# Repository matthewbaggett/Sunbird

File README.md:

# Sunbird

Version: rev11.

## Technical information

This is a board designed around an off-the-shelf ESP8266 ESP-12(E|F|S) module.

### Component choices

 * [ESP8266](./docs/esp8266ex.pdf) single-core 160Mhz 32 bit microcontroller with Wifi, 32K RAM and 4MB ROM as main CPU.
 * 2x 5050 RGB notification LEDs on either side of the PCB at the rear end
 * USB C charge and programming port.
 * [CH340g](./docs/CH340DS1.pdf) USB UART controller, with automatic reset circuitry for programming CPU.
 * [FS312F-G](./docs/FS312F-G-DS-10_EN.pdf) (and associated double-mosfet) short circuit protection circuitry. This also provides overcharge/overdischarge protection
 * [TP4056](./docs/TP4056.pdf) li-ion battery charger circuit. CHRG and STDBY signals passed through to CPU.
 * [ADXL345](./docs/ADXL345.pdf) Accellerometer for smart-power-off and usage detection using i2c bus with interrupt line.
 * [FM116B](./docs/FM116B.pdf) motor driver H-bridge IC. Warning: Datasheet almost entirely in Chinese.
 * Integrated 500mA fuse on PCB.
 * Standardised around 0603 size components where possible.
 * [Tag-Connect TC2030 no-legs](http://www.tag-connect.com/TC2030-MCP-NL) zero-pcb-parts connector used for programming and debugging before the CH340G is brought up, and for diagnosis when the CH340G is not populated, or otherwise unavailable due to failure.

### Technical features

 * Ability to field-program in-situ using USB bus.
 * Ability to OTA (Over The Air) program device.
 * Ability to sample battery voltage without incurring passive current draw, using 2 high-resistence resistors and a single transitor to enable battery sampling.
 * Ability to run while charging battery.
 * Ability to show status using RGB colour LED on both sides of circuit board.

### Known issues
 * 3.3v regulator has been problematic so far. Hopefully resolved in rev11.
 * 5050 RGB LEDs don't have consistent pinout of which colour channel is on which pin, meaning the value of R8020-22 are unpredictable, and subject to change before assembly. I have debated using WS2812B or similar as a replacement, but increasing parts cost and program complexity deterred me.

### Licencing

Sunbird is licenced under the [Open Hardware TAPR licence](./LICENCE.md).

## PCB

## Schematics

### Processor

### Battery Charger Circuit

### Power Regulator

### Motor Driver

### USB UART

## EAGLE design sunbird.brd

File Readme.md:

# Sunbird

Version: rev11.

## Technical information

This is a board designed around an off-the-shelf ESP8266 ESP-12(E|F|S) module.

### Component choices

 * [ESP8266](./docs/esp8266ex.pdf) single-core 160Mhz 32 bit microcontroller with Wifi, 32K RAM and 4MB ROM as main CPU.
 * 2x 5050 RGB notification LEDs on either side of the PCB at the rear end
 * USB C charge and programming port.
 * [CH340g](./docs/CH340DS1.pdf) USB UART controller, with automatic reset circuitry for programming CPU.
 * [FS312F-G](./docs/FS312F-G-DS-10_EN.pdf) (and associated double-mosfet) short circuit protection circuitry. This also provides overcharge/overdischarge protection
 * [TP4056](./docs/TP4056.pdf) li-ion battery charger circuit. CHRG and STDBY signals passed through to CPU.
 * [ADXL345](./docs/ADXL345.pdf) Accellerometer for smart-power-off and usage detection using i2c bus with interrupt line.
 * [FM116B](./docs/FM116B.pdf) motor driver H-bridge IC. Warning: Datasheet almost entirely in Chinese.
 * Integrated 500mA fuse on PCB.
 * Standardised around 0603 size components where possible.
 * [Tag-Connect TC2030 no-legs](http://www.tag-connect.com/TC2030-MCP-NL) zero-pcb-parts connector used for programming and debugging before the CH340G is brought up, and for diagnosis when the CH340G is not populated, or otherwise unavailable due to failure.

### Technical features

 * Ability to field-program in-situ using USB bus.
 * Ability to OTA (Over The Air) program device.
 * Ability to sample battery voltage without incurring passive current draw, using 2 high-resistence resistors and a single transitor to enable battery sampling.
 * Ability to run while charging battery.
 * Ability to show status using RGB colour LED on both sides of circuit board.

### Known issues
 * 3.3v regulator has been problematic so far. Hopefully resolved in rev11.
 * 5050 RGB LEDs don't have consistent pinout of which colour channel is on which pin, meaning the value of R8020-22 are unpredictable, and subject to change before assembly. I have debated using WS2812B or similar as a replacement, but increasing parts cost and program complexity deterred me.

## PCB
![Render][./images/3d.png]
![PCB view][./images/pcb.png]

## Schematics

### Processor
![Processor][./images/processor.png]

### Battery Charger Circuit
![Battery Charger][./images/battery_charger.png]

### Power Regulator
![Power Regulator][./images/power_regulator.png]

### Motor Driver
![Motor Driver][./images/motor_driver.png]

### USB UART
![USB UART][./images/usb_uart_ch340g.png]

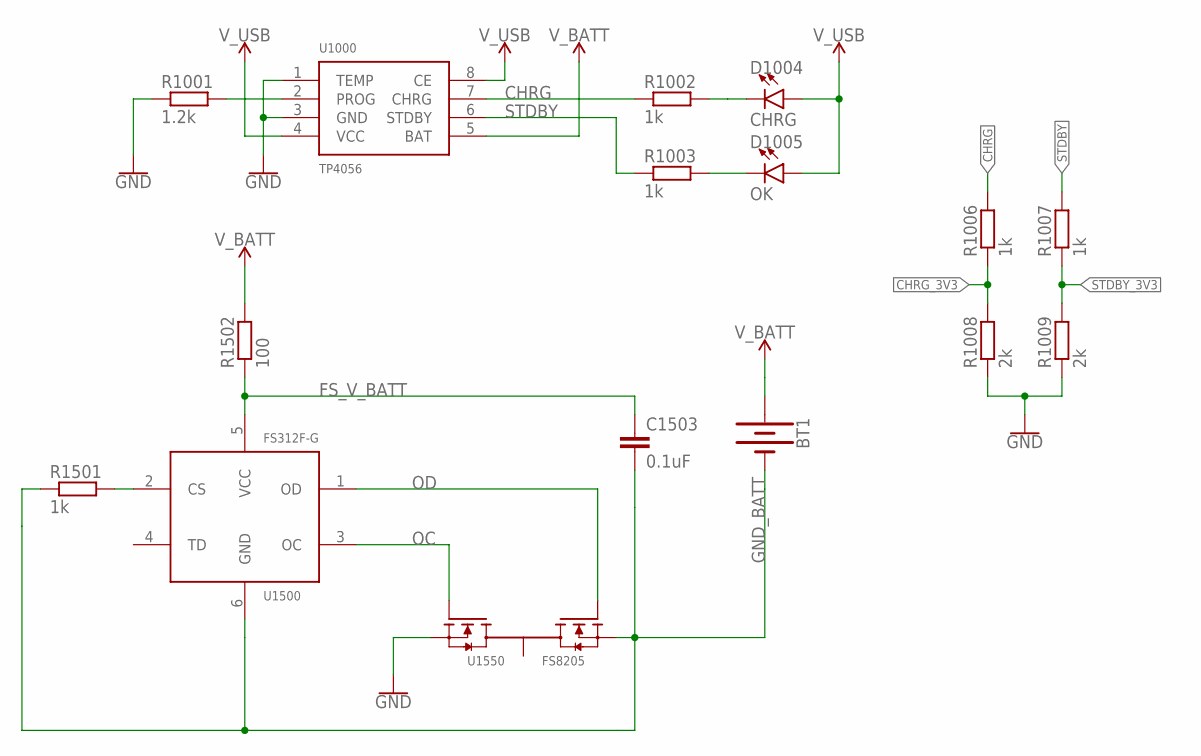
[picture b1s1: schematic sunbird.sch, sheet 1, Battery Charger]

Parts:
BT1: BATTERY-18650; BATTERY_18650-HOLDER
C1503: 0.1uF; C0603
D1004: CHRG; LED-0603
D1005: OK; LED-0603
R1001: 1.2k; R0603
R1002, R1003, R1006, R1007, R1501: 1k; R0603
R1008, R1009: 2k; R0603
R1502: 100; R0603
U1000: TP4056; SOP-8-THERMAL
U1500: FS312F-G; SOT23-6
U1550: FS8205; SOT23-6

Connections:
CHRG: R1002.1, R1006.2, U1000.7 (CHRG)
CHRG_3V3: R1006.1, R1008.2; also elsewhere on the board
FS_CS: R1501.2, U1500.2 (CS)
FS_V_BATT: C1503.1, R1502.1, U1500.5 (VCC)
GND: R1001.1, R1008.1, R1009.1, U1000.1 (TEMP), U1000.3 (GND), U1550.1 (S1); also elsewhere on the board
GND_BATT: BT1.GND@1 (-), C1503.2, R1501.1, U1500.6 (GND), U1550.3 (S2)
unnamed: R1001.2, U1000.2 (PROG)
unnamed: D1005.C, R1003.2
unnamed: D1004.C, R1002.2
OC: U1500.3 (OC), U1550.6 (G1)
OD: U1500.1 (OD), U1550.4 (G2)
STDBY: R1003.1, R1007.2, U1000.6 (STDBY)
STDBY_3V3: R1007.1, R1009.2; also elsewhere on the board
V_BATT: BT1.PWR@1 (+), R1502.2, U1000.5 (BAT); also elsewhere on the board
V_USB: D1004.A, D1005.A, U1000.4 (VCC), U1000.8 (CE); also elsewhere on the board

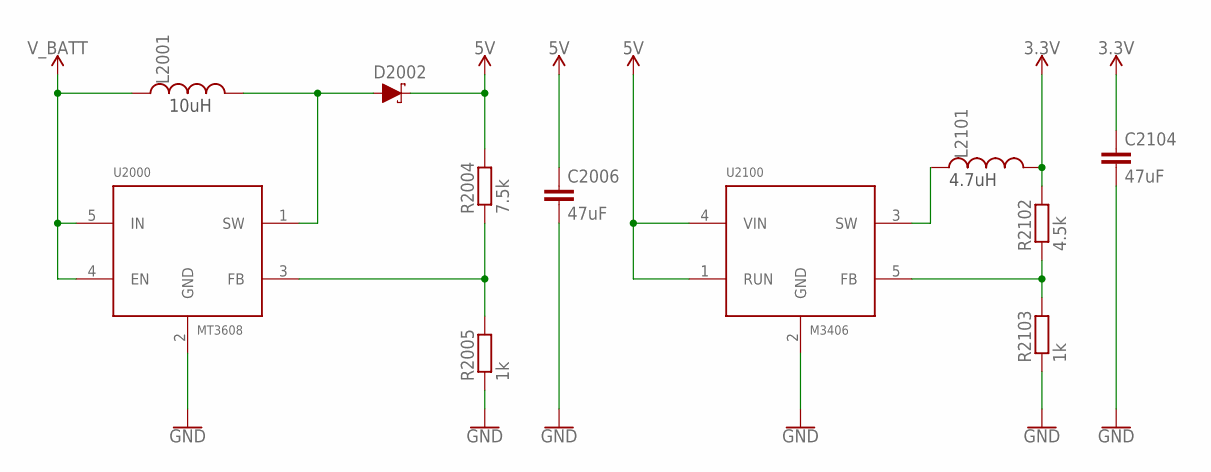
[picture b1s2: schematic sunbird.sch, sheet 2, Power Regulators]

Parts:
C2006, C2104: 47uF; C0603
D2002: DIODE-SCHOTTKY-PMEG4005EJ; SOD-323
L2001: 10uH; INDUCTOR_3.0X3.0
L2101: 4.7uH; INDUCTOR_3.0X3.0
R2004: 7.5k; R0603
R2005, R2103: 1k; R0603
R2102: 4.5k; R0603
U2000: MT3608; SOT23-6
U2100: M3406; SOT23-5

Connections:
3.3V: C2104.1, L2101.P$2 (2), R2102.2; also elsewhere on the board
5V: C2006.1, D2002.C, R2004.2, U2100.1 (RUN), U2100.4 (VIN); also elsewhere on the board
BUCK: D2002.A, L2001.P$2 (2), U2000.1 (SW)
GND: C2006.2, C2104.2, R2005.1, R2103.1, U2000.2 (GND), U2100.2 (GND); also elsewhere on the board
unnamed: L2101.P$1 (1), U2100.3 (SW)
unnamed: R2102.1, R2103.2, U2100.5 (FB)
unnamed: R2004.1, R2005.2, U2000.3 (FB)
V_BATT: L2001.P$1 (1), U2000.4 (EN), U2000.5 (IN); also elsewhere on the board

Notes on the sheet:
10uH
4.7uH

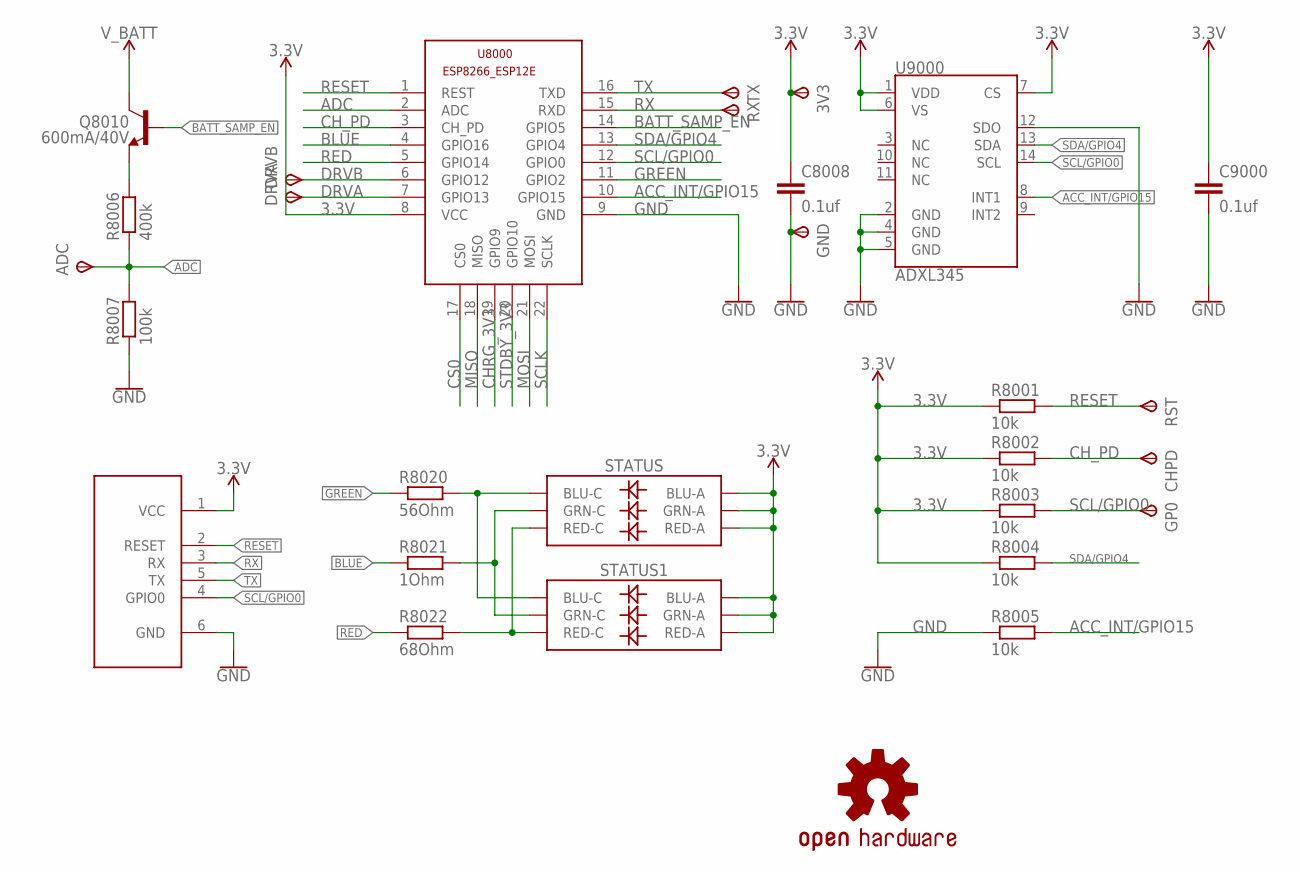
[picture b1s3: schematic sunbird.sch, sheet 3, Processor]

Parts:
3V3: TPSTP10R; TP10R
ADC: TPSTP10R; TP10R
C8008, C9000: 0.1uf; C0603
CHPD: TPSTP10R; TP10R
DEBUG: ESP8266_PROGRAMMER; TC2030-IDC-NL
DRVA: TPSTP10R; TP10R
DRVB: TPSTP10R; TP10R
GND: TPSTP10R; TP10R
GP0: TPSTP10R; TP10R
LOGO1: OSHW-LOGOS; OSHW-LOGO-S
Q8010: 600mA/40V; SOT23-3
R8001, R8002, R8003, R8004, R8005: 10k; R0603
R8006: 400k; R0603
R8007: 100k; R0603
R8020: 56Ohm; R0603
R8021: 1Ohm; R0603
R8022: 68Ohm; R0603
RST: TPSTP10R; TP10R
RX: TPSTP10R; TP10R
STATUS, STATUS1: LED-RGBNO_IC; LED-TRICOLOR-5050
TX: TPSTP10R; TP10R
U8000: ESP8266-12EESP8266-ESP12E; ESP8266-ESP12E
U9000: ADXL345; LGA-14

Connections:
3.3V: 3V3.TP, C8008.1, C9000.1, DEBUG.1 (VCC), R8001.1, R8002.1, R8003.1, R8004.1, STATUS.1 (GRN-A), STATUS.2 (RED-A), STATUS.3 (BLU-A), STATUS1.1 (GRN-A), STATUS1.2 (RED-A), STATUS1.3 (BLU-A), U8000.8 (VCC), U9000.1 (VDD), U9000.6 (VS), U9000.7 (CS); also elsewhere on the board
ACC_INT/GPIO15: R8005.2, U8000.10 (GPIO15), U9000.8 (INT1)
ADC: ADC.TP, R8006.1, R8007.2, U8000.2 (ADC)
BATT_SAMP_EN: Q8010.1 (B), U8000.14 (GPIO5)
BLUE: R8021.1, U8000.4 (GPIO16)
CHRG_3V3: U8000.19 (GPIO9); also elsewhere on the board
CH_PD: CHPD.TP, R8002.2, U8000.3 (CH_PD)
CS0: U8000.17 (CS0)
DRVA: DRVA.TP, U8000.7 (GPIO13); also elsewhere on the board
DRVB: DRVB.TP, U8000.6 (GPIO12); also elsewhere on the board
GND: C8008.2, C9000.2, DEBUG.6 (GND), GND.TP, R8005.1, R8007.1, U8000.9 (GND), U9000.2 (GND), U9000.4 (GND), U9000.5 (GND), U9000.12 (SDO); also elsewhere on the board
GREEN: R8020.1, U8000.11 (GPIO2)
MISO: U8000.18 (MISO)
MOSI: U8000.21 (MOSI)
unnamed: Q8010.2 (E), R8006.2
unnamed: R8020.2, STATUS.4 (BLU-C), STATUS1.4 (BLU-C)
unnamed: R8021.2, STATUS.6 (GRN-C), STATUS1.6 (GRN-C)
unnamed: R8022.2, STATUS.5 (RED-C), STATUS1.5 (RED-C)
RED: R8022.1, U8000.5 (GPIO14)
RESET: DEBUG.2 (RESET), R8001.2, RST.TP, U8000.1 (REST); also elsewhere on the board
RX: DEBUG.3 (RX), RX.TP, U8000.15 (RXD); also elsewhere on the board
SCL/GPIO0: DEBUG.4 (GPIO0), GP0.TP, R8003.2, U8000.12 (GPIO0), U9000.14 (SCL); also elsewhere on the board
SCLK: U8000.22 (SCLK)
SDA/GPIO4: R8004.2, U8000.13 (GPIO4), U9000.13 (SDA)
STDBY_3V3: U8000.20 (GPIO10); also elsewhere on the board
TX: DEBUG.5 (TX), TX.TP, U8000.16 (TXD); also elsewhere on the board
V_BATT: Q8010.3 (C); also elsewhere on the board

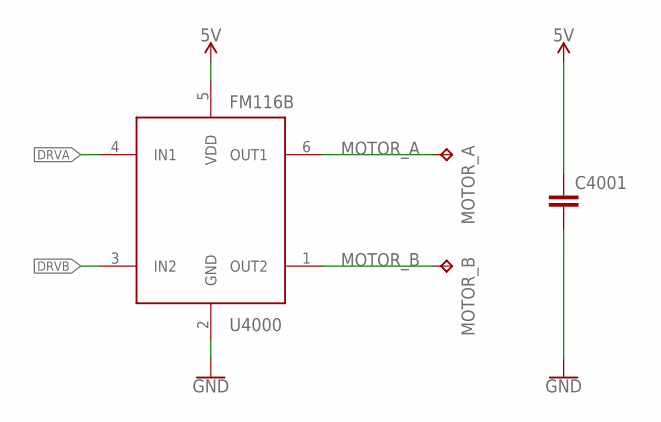
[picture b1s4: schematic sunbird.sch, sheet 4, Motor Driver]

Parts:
C4001: C-EUC0603; C0603
MOTOR_A: TPTP20SQ; TP20SQ
MOTOR_B: TPTP20SQ; TP20SQ
U4000: FM116B; SOT23-6

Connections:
5V: C4001.1, U4000.5 (VDD); also elsewhere on the board
DRVA: U4000.4 (IN1); also elsewhere on the board
DRVB: U4000.3 (IN2); also elsewhere on the board
GND: C4001.2, U4000.2 (GND); also elsewhere on the board
MOTOR_A: MOTOR_A.TP, U4000.6 (OUT1)
MOTOR_B: MOTOR_B.TP, U4000.1 (OUT2)

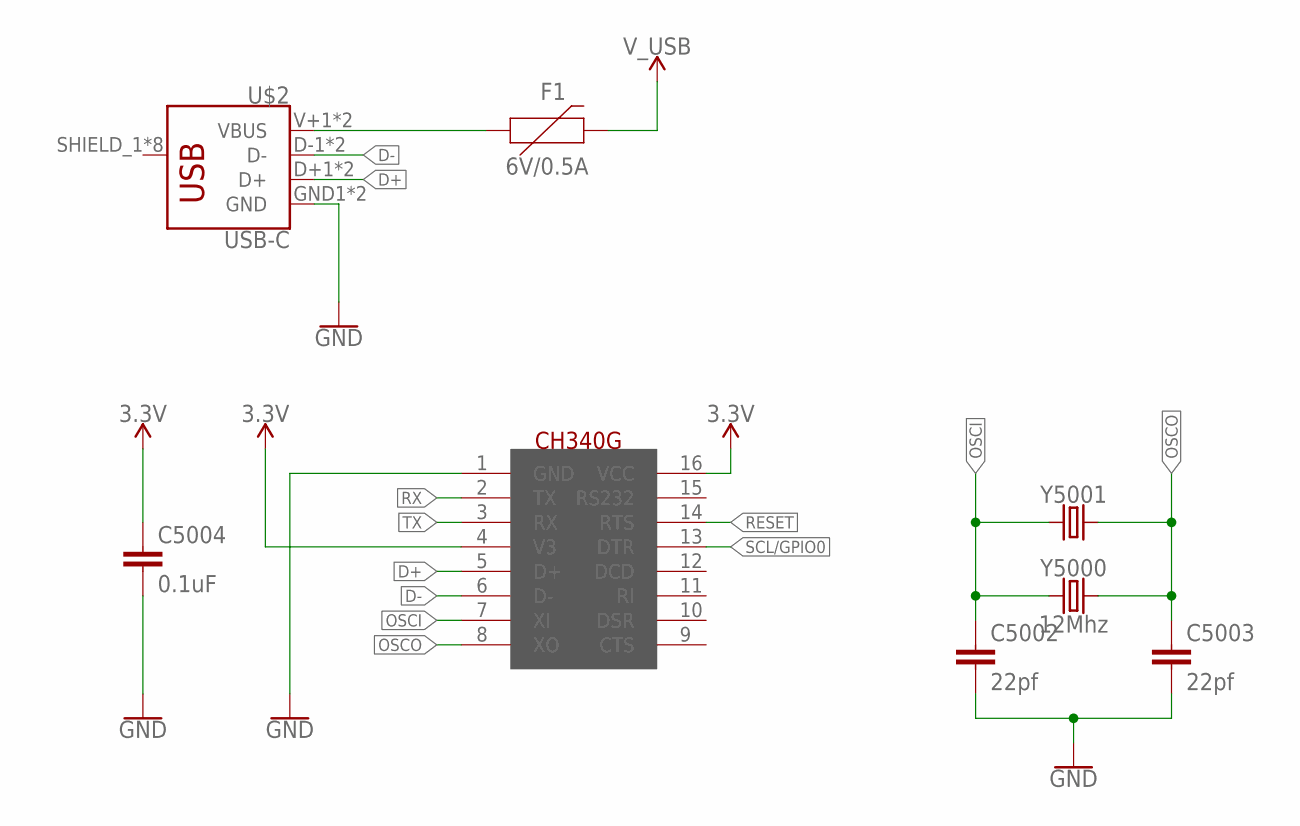
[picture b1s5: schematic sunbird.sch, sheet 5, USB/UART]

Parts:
C5002, C5003: 22pf; C0603
C5004: 0.1uF; C0603
F1: 6V/0.5A; 1206
U5000: CH340G; SOIC16
U$2: USB-C; USB_C-XKBENTERPRISEU262-16XN-4BVC11
Y5000: 12Mhz; HC49UP
Y5001: CRYSTALPTH-HC49UV; HC49U

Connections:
3.3V: C5004.1, U5000.4 (V3), U5000.16 (VCC); also elsewhere on the board
D+: U5000.5 (D+), U$2.D+1 (D+), U$2.D+2 (D+)
D-: U5000.6 (D-), U$2.D-1 (D-), U$2.D-2 (D-)
GND: C5002.2, C5003.2, C5004.2, U5000.1 (GND), U$2.GND1 (GND), U$2.GND2 (GND); also elsewhere on the board
OSCI: C5002.1, U5000.7 (XI), Y5000.1, Y5001.1
OSCO: C5003.1, U5000.8 (XO), Y5000.2, Y5001.2
RESET: U5000.14 (RTS); also elsewhere on the board
RX: U5000.2 (TX); also elsewhere on the board
SCL/GPIO0: U5000.13 (DTR); also elsewhere on the board
TX: U5000.3 (RX); also elsewhere on the board
V_USB: F1.2; also elsewhere on the board
V_USB_UNFUSED: F1.1, U$2.V+1 (VBUS), U$2.V+2 (VBUS)

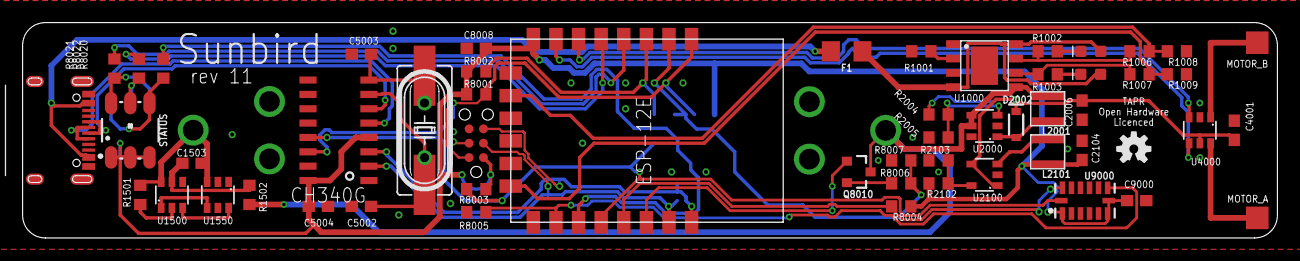
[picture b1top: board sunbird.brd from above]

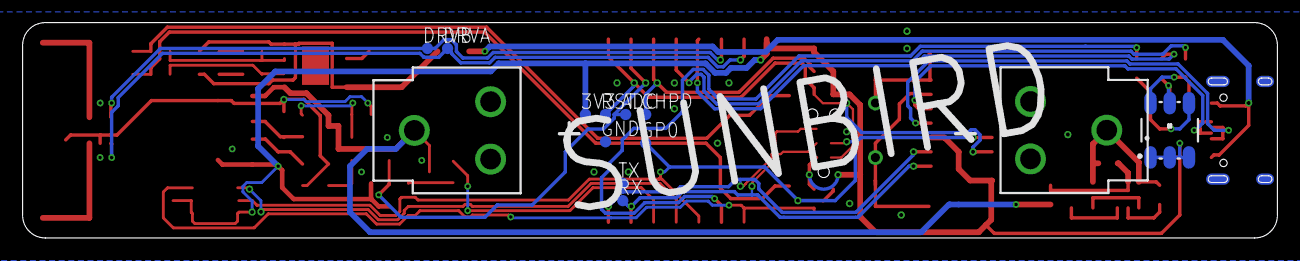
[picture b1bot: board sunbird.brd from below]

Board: 2 copper layers, 111.0 x 19.1 mm, 68 parts (12 on the bottom side), 46 nets.

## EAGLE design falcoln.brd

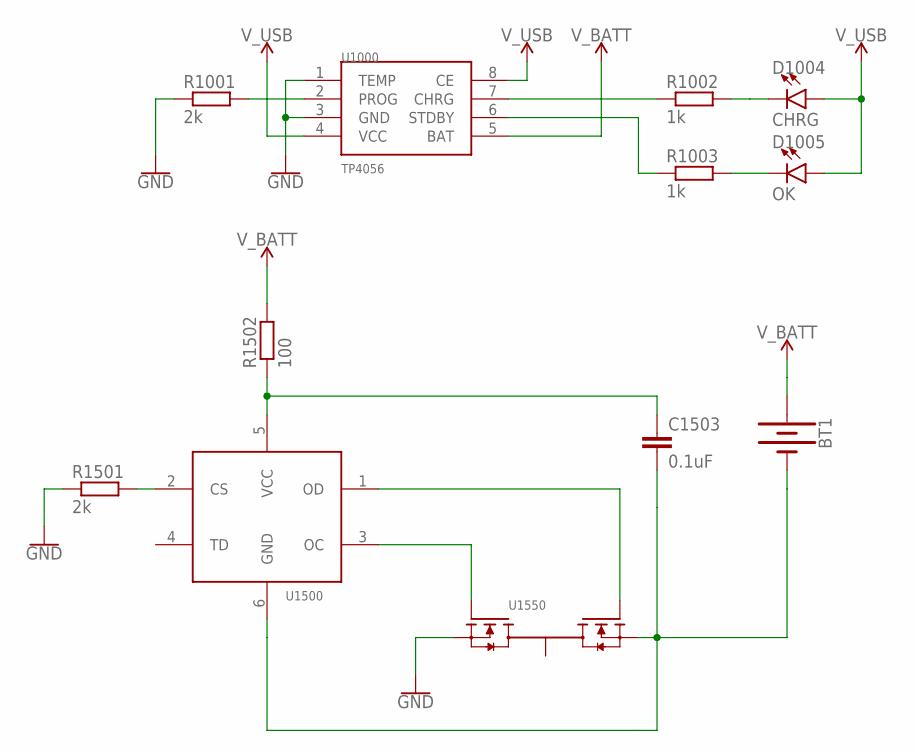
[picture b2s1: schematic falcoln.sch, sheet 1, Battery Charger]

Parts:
BT1: BATTERY-18650; BATTERY_18650-HOLDER
C1503: 0.1uF; C0603
D1004: CHRG; LED-0603
D1005: OK; LED-0603
R1001, R1501: 2k; R0603
R1002, R1003: 1k; R0603
R1502: 100; R0603
U1000: TP4056; SOP-8
U1500: FS312F-G; SOT23-6
U1550: FS8205; SOT23-6

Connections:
GND: R1001.1, R1501.1, U1000.1 (TEMP), U1000.3 (GND), U1550.1 (S1); also elsewhere on the board
unnamed: U1500.3 (OC), U1550.6 (G1)
unnamed: R1002.1, U1000.7 (CHRG)
unnamed: R1003.1, U1000.6 (STDBY)
unnamed: R1001.2, U1000.2 (PROG)
unnamed: BT1.GND@1 (-), C1503.2, U1500.6 (GND), U1550.3 (S2)
unnamed: D1005.C, R1003.2
unnamed: D1004.C, R1002.2
unnamed: U1500.1 (OD), U1550.4 (G2)
unnamed: C1503.1, R1502.1, U1500.5 (VCC)
unnamed: R1501.2, U1500.2 (CS)
V_BATT: BT1.PWR@1 (+), R1502.2, U1000.5 (BAT); also elsewhere on the board
V_USB: D1004.A, D1005.A, U1000.4 (VCC), U1000.8 (CE); also elsewhere on the board

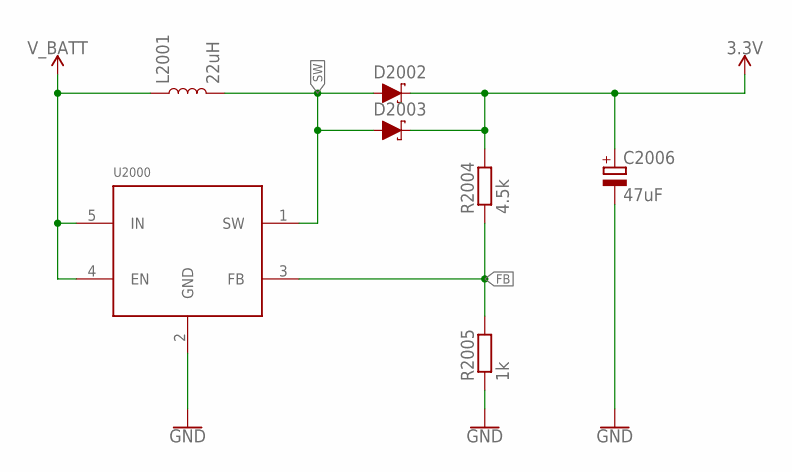
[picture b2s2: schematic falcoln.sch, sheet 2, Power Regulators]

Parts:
C2006: 47uF; UD-5X5,8_NICHICON
D2002, D2003: DIODE-SCHOTTKY-PMEG4005EJ; SOD-323
L2001: 22uH; SRN6045
R2004: 4.5k; R0603
R2005: 1k; R0603
U2000: MT3608; SOT23-6

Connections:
3.3V: C2006.+, D2002.C, D2003.C, R2004.2; also elsewhere on the board
FB: R2004.1, R2005.2, U2000.3 (FB)
GND: C2006.-, R2005.1, U2000.2 (GND); also elsewhere on the board
SW: D2002.A, D2003.A, L2001.2, U2000.1 (SW)
V_BATT: L2001.1, U2000.4 (EN), U2000.5 (IN); also elsewhere on the board

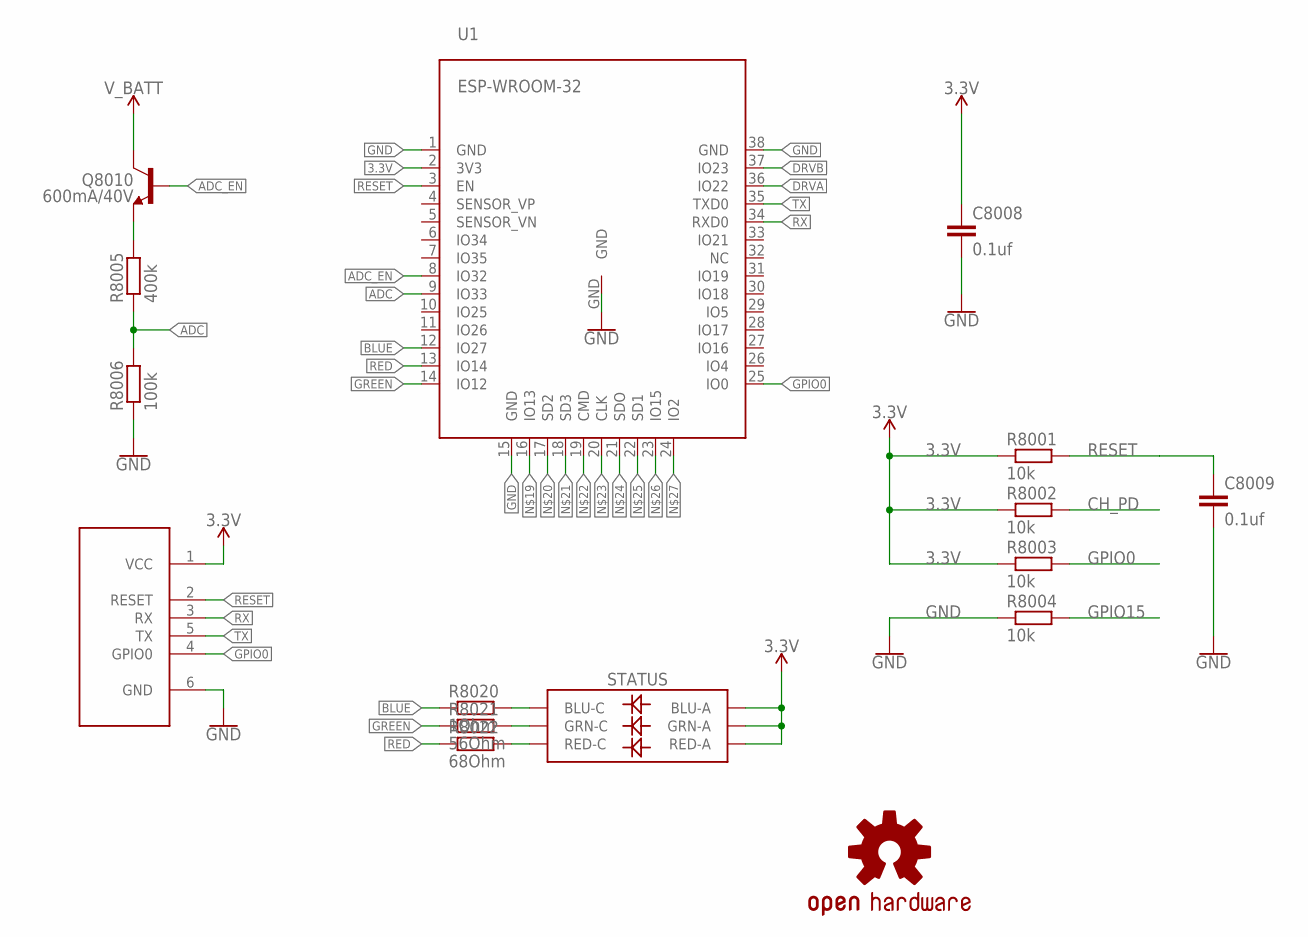
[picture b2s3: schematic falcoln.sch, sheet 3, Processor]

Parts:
C8008, C8009: 0.1uf; C0603
LOGO1: OSHW-LOGOS; OSHW-LOGO-S
Q8010: 600mA/40V; SOT23-3
R8001, R8002, R8003, R8004: 10k; R0603
R8005: 400k; R0603
R8006: 100k; R0603
R8020: 1Ohm; R0603
R8021: 56Ohm; R0603
R8022: 68Ohm; R0603
STATUS: LED-RGBNO_IC; LED-TRICOLOR-5050
U1: ESP-WROOM-32
U$1: ESP8266_PROGRAMMER; TC2030-IDC-NL

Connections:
3.3V: C8008.1, R8001.1, R8002.1, R8003.1, STATUS.1 (GRN-A), STATUS.2 (RED-A), STATUS.3 (BLU-A), U1.2 (3V3), U$1.1 (VCC); also elsewhere on the board
ADC: R8005.1, R8006.2, U1.9 (IO33)
ADC_EN: Q8010.1 (B), U1.8 (IO32)
BLUE: R8020.1, U1.12 (IO27)
CH_PD: R8002.2
DRVA: U1.36 (IO22); also elsewhere on the board
DRVB: U1.37 (IO23); also elsewhere on the board
GND: C8008.2, C8009.2, R8004.1, R8006.1, U1.1 (GND), U1.15 (GND), U1.38 (GND), U1.GND, U$1.6 (GND); also elsewhere on the board
GPIO0: R8003.2, U1.25 (IO0), U$1.4 (GPIO0); also elsewhere on the board
GPIO15: R8004.2
GREEN: R8021.1, U1.14 (IO12)
unnamed: Q8010.2 (E), R8005.2
unnamed: R8020.2, STATUS.4 (BLU-C)
unnamed: R8021.2, STATUS.6 (GRN-C)
unnamed: R8022.2, STATUS.5 (RED-C)
RED: R8022.1, U1.13 (IO14)
RESET: C8009.1, R8001.2, U1.3 (EN), U$1.2 (RESET); also elsewhere on the board
RX: U1.34 (RXD0), U$1.3 (RX); also elsewhere on the board
TX: U1.35 (TXD0), U$1.5 (TX); also elsewhere on the board
V_BATT: Q8010.3 (C); also elsewhere on the board

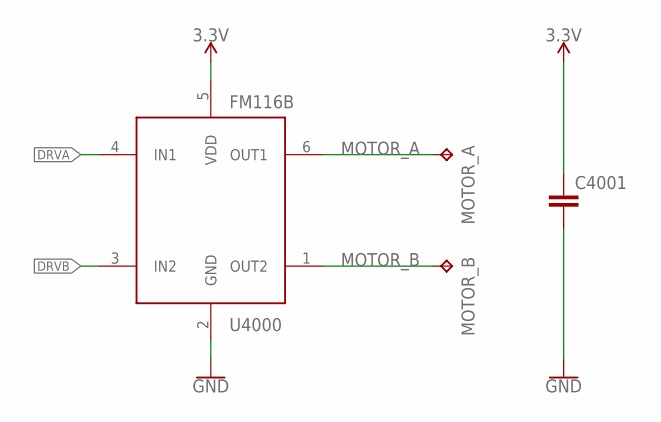
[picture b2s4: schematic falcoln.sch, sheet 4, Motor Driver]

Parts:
C4001: C-EUC0603; C0603
MOTOR_A: TPTP20SQ; TP20SQ
MOTOR_B: TPTP20SQ; TP20SQ
U4000: FM116B; SOT23-6

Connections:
3.3V: C4001.1, U4000.5 (VDD); also elsewhere on the board
DRVA: U4000.4 (IN1); also elsewhere on the board
DRVB: U4000.3 (IN2); also elsewhere on the board
GND: C4001.2, U4000.2 (GND); also elsewhere on the board
MOTOR_A: MOTOR_A.TP, U4000.6 (OUT1)
MOTOR_B: MOTOR_B.TP, U4000.1 (OUT2)

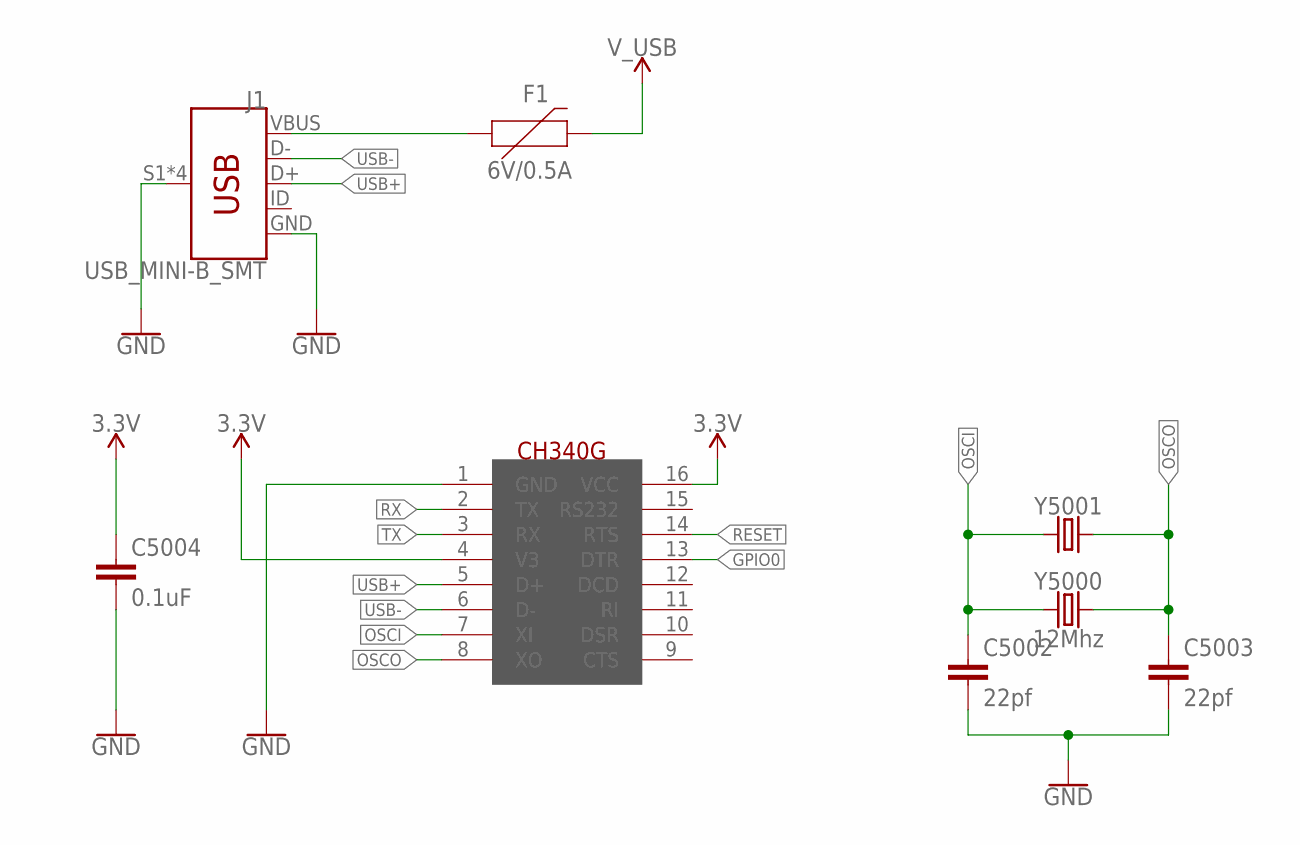
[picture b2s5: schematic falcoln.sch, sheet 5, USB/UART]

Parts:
C5002, C5003: 22pf; C0603
C5004: 0.1uF; C0603
F1: 6V/0.5A; 1206
J1: USB_MINI-B_SMT; USB-MINIB
U5000: CH340G; SOIC16
Y5000: 12Mhz; HC49UP
Y5001: CRYSTALPTH-HC49UV; HC49U

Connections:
3.3V: C5004.1, U5000.4 (V3), U5000.16 (VCC); also elsewhere on the board
GND: C5002.2, C5003.2, C5004.2, J1.GND, J1.S1 (SHIELD), J1.S2 (SHIELD), J1.S3 (SHIELD), J1.S4 (SHIELD), U5000.1 (GND); also elsewhere on the board
GPIO0: U5000.13 (DTR); also elsewhere on the board
OSCI: C5002.1, U5000.7 (XI), Y5000.1, Y5001.1
OSCO: C5003.1, U5000.8 (XO), Y5000.2, Y5001.2
RESET: U5000.14 (RTS); also elsewhere on the board
RX: U5000.2 (TX); also elsewhere on the board
TX: U5000.3 (RX); also elsewhere on the board
USB+: J1.D+, U5000.5 (D+)
USB-: J1.D-, U5000.6 (D-)
V_USB: F1.2; also elsewhere on the board
V_USB_UNFUSED: F1.1, J1.VBUS

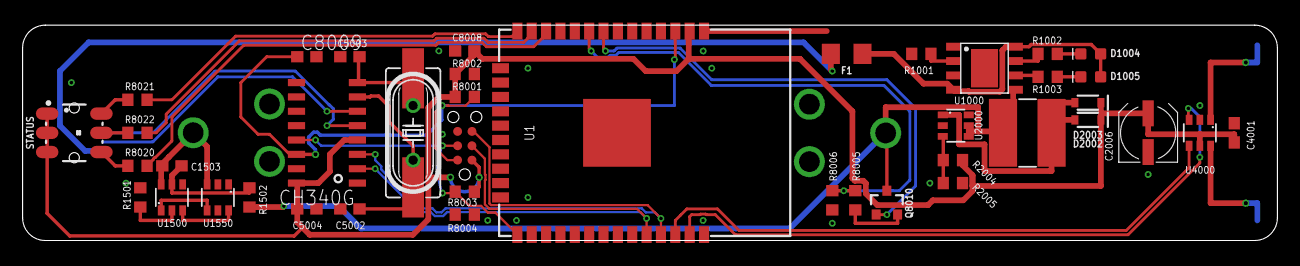
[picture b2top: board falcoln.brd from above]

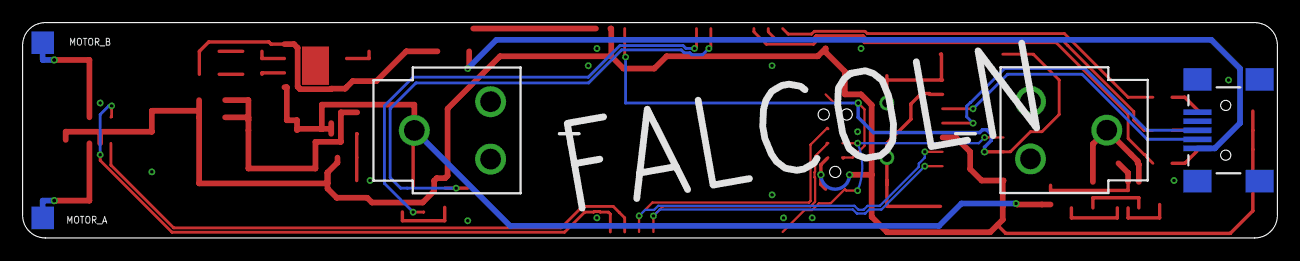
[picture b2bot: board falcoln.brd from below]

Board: 2 copper layers, 111.0 x 19.1 mm, 47 parts (4 on the bottom side), 38 nets.

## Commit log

2018-08-14 Initial schematics
2018-08-14 Getting there
2018-08-14 Almost done
2018-08-16 Sunbird. Again.
2018-08-16 Rotated the logo just a bit
2018-08-16 Add a status LED
2018-08-16 Renumber status resistors, reposition labels
2018-08-16 Remove uneeded labels
2018-08-16 Change LED signal names for clarity.
2018-08-16 More beautification
2018-08-16 Move logo to rear, bigger
2018-08-16 Move logo to rear, bigger and more center-er
2018-08-16 Rename GPIO5 to BATT_SAMP_EN
2018-08-16 Board ordered
2018-08-16 yeah, lets keep zipped gerbers
2018-09-15 Revise the mess I made of the power regulators, add accellerometer. Motor now has a beefier 5v rail.
2018-09-17 Missed changes
2018-09-22 Why did I not commit the source and assets?
2018-09-22 more bits
2018-10-11 Adding image exports
2018-10-28 Missed commits
2018-12-26 Reworking - adding oled.. doesn't work tho
2018-12-26 Changing ssd1306 lib... unbuggered some output.. unbuggered timers.. unbuggered debug a bit
2018-12-26 Debug packets now being sent - but the printf'd data is bad.
2018-12-26 Working i2c oled display - runs a test loop
2018-12-26 Better console outputs
2018-12-26 Tring to make AP work
2018-12-26 Buttplug AP now works.
2018-12-26 Renaming AP for stealth
2018-12-26 Working display demo
2018-12-27 Initial OTA
2019-01-25 Revise PCB to use inductors + 47uF 0603 "miracle" caps from LCSC.
2019-01-25 Remove Falcoln related stuff
2019-01-25 Removing sensor array
2019-01-25 Get rid of solderpaste gerber
2019-01-25 Merged into DongsOS
2019-01-25 Rejig layout, add measurement indexes
2019-01-26 Futzing around with via placement
2019-01-26 Added USB-C socket. Put a copy of the RGB LED on the rear side. Rejigged components.
2019-01-26 Regenerated all exported images
2019-01-26 Added a 3d render
2019-01-26 documentation
2019-01-26 Fix broken images
2019-01-26 Adding TAPR licence
2019-01-26 Add TAPR licence text to PCB silk

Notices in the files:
parts and their libraries:
SparkFun-Batteries: Licensing: Creative Commons ShareAlike 4.0 International - https://creativecommons.org/licenses/by-sa/4.0
